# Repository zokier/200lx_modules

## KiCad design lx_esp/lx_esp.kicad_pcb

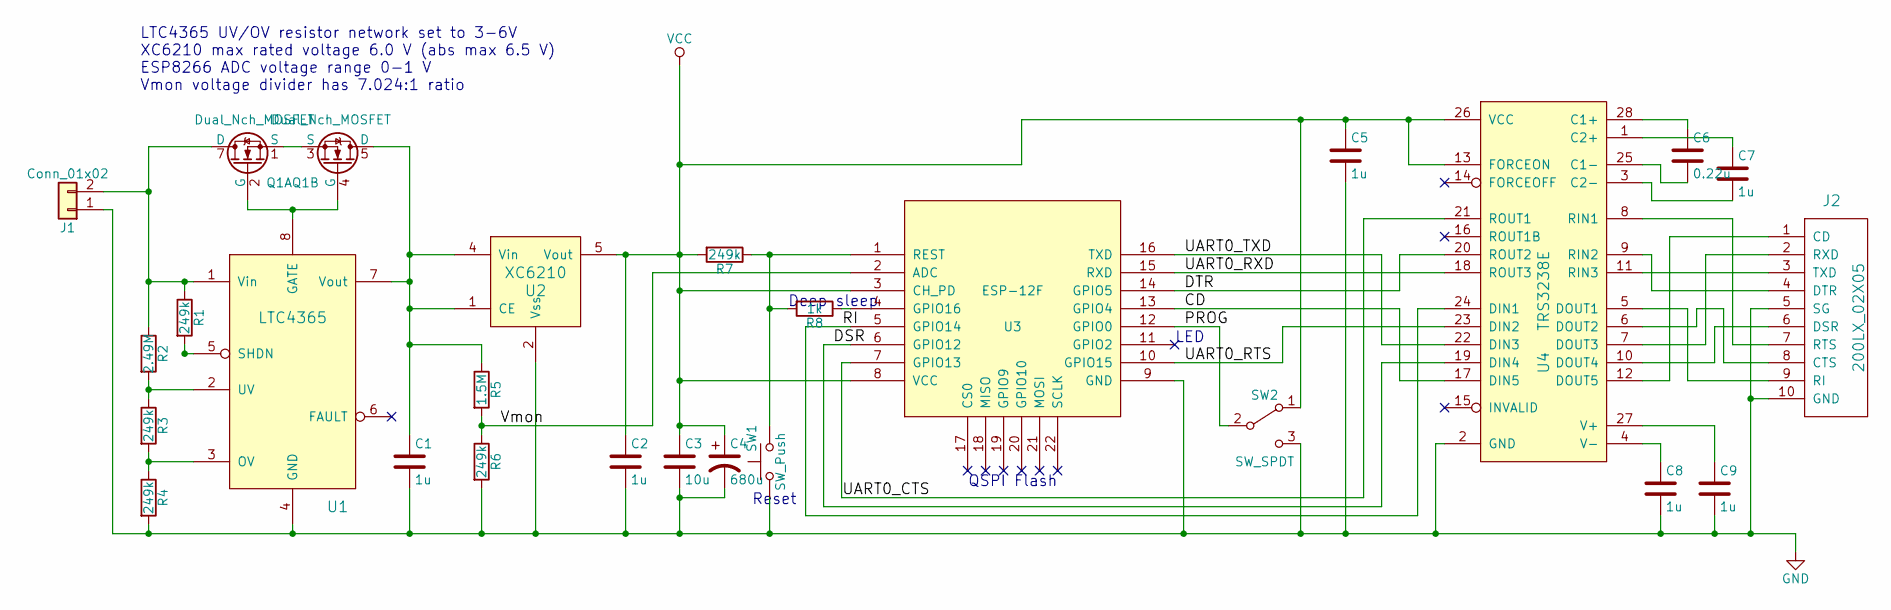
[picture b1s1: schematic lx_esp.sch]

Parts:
C1, C2, C5, C7, C8, C9: 1u; C_0805_HandSoldering
C3: 10u; C_0805_HandSoldering
C4: 680u; CP_Radial_D10.0mm_P5.00mm
C6: 0.22u; C_0805_HandSoldering
J1: Conn_01x02; JST_PH_S2B-PH-K_02x2.00mm_Angled
J2: 200LX_02X05; CONN_02x05_2mm
Q1: Dual_Nch_MOSFET; SOIC-8_3.9x4.9mm_Pitch1.27mm
R1, R3, R4, R6, R7: 249k; R_0805_HandSoldering
R2: 2.49M; R_0805_HandSoldering
R5: 1.5M; R_0805_HandSoldering
R8: 1k; R_0805_HandSoldering
SW1: SW_Push; TL3305
SW2: SW_SPDT; CL-SB-12B-02T
U1: LTC4365; TSOT-23-8_HandSoldering
U2: XC6210; SOT-89-5_Housing_Handsoldering
U3: ESP-12F; ESP-12E_SMD
U4: TRS3238E; (T)SSOP-28

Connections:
/CD: U3.13 (GPIO4), U4.17 (DIN5)
/DSR: U3.6 (GPIO12), U4.19 (DIN4)
/DTR: U3.14 (GPIO5), U4.20 (ROUT2)
/PROG: SW2.2 (B), U3.12 (GPIO0)
/RI: U3.5 (GPIO14), U4.24 (DIN1)
/UART0_CTS: U3.7 (GPIO13), U4.21 (ROUT1)
/UART0_RTS: U3.10 (GPIO15), U4.23 (DIN2)
/UART0_RXD: U3.15 (RXD), U4.18 (ROUT3)
/UART0_TXD: U3.16 (TXD), U4.22 (DIN3)
/Vmon: R5.2, R6.1, U3.2 (ADC)
GND: C1.2, C2.2, C3.2, C4.2, C5.2, C8.2, C9.2, J1.1, J2.5 (SG), J2.10 (GND), R4.2, R6.2, SW1.1, SW2.3 (C), U1.4 (GND), U2.2 (Vss), U3.9 (GND), U4.2 (GND)
unnamed: C1.1, Q1.5 (D), Q1.6 (D), R5.1, U1.7 (Vout), U2.1 (CE), U2.4 (Vin)
unnamed: C6.1, U4.28 (C1+)
unnamed: C6.2, U4.25 (C1-)
unnamed: C7.1, U4.1 (C2+)
unnamed: C7.2, U4.3 (C2-)
unnamed: C8.1, U4.4 (V-)
unnamed: C9.1, U4.27 (V+)
unnamed: J1.2, Q1.7 (D), Q1.8 (D), R1.1, R2.1, U1.1 (Vin)
unnamed: J2.1 (CD), U4.12 (DOUT5)
unnamed: J2.2 (RXD), U4.7 (DOUT3)
unnamed: J2.3 (TXD), U4.11 (RIN3)
unnamed: J2.4 (DTR), U4.9 (RIN2)
unnamed: J2.6 (DSR), U4.10 (DOUT4)
unnamed: J2.7 (RTS), U4.8 (RIN1)
unnamed: J2.8 (CTS), U4.6 (DOUT2)
unnamed: J2.9 (RI), U4.5 (DOUT1)
unnamed: Q1.1 (S), Q1.3 (S)
unnamed: Q1.2 (G), Q1.4 (G), U1.8 (GATE)
unnamed: R1.2, U1.5 (SHDN)
unnamed: R2.2, R3.1, U1.2 (UV)
unnamed: R3.2, R4.1, U1.3 (OV)
unnamed: R7.1, R8.2, SW1.2, U3.1 (REST)
unnamed: R8.1, U3.4 (GPIO16)
VCC: C2.1, C3.1, C4.1, C5.1, R7.2, SW2.1 (A), U2.5 (Vout), U3.3 (CH_PD), U3.8 (VCC), U4.13 (FORCEON), U4.26 (VCC)

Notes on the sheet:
LED
QSPI Flash
Deep sleep
Reset
LTC4365 UV/OV resistor network set to 3-6V XC6210 max rated voltage 6.0 V (abs max 6.5 V) ESP8266 ADC voltage range 0-1 V Vmon voltage divider has 7.024:1 ratio

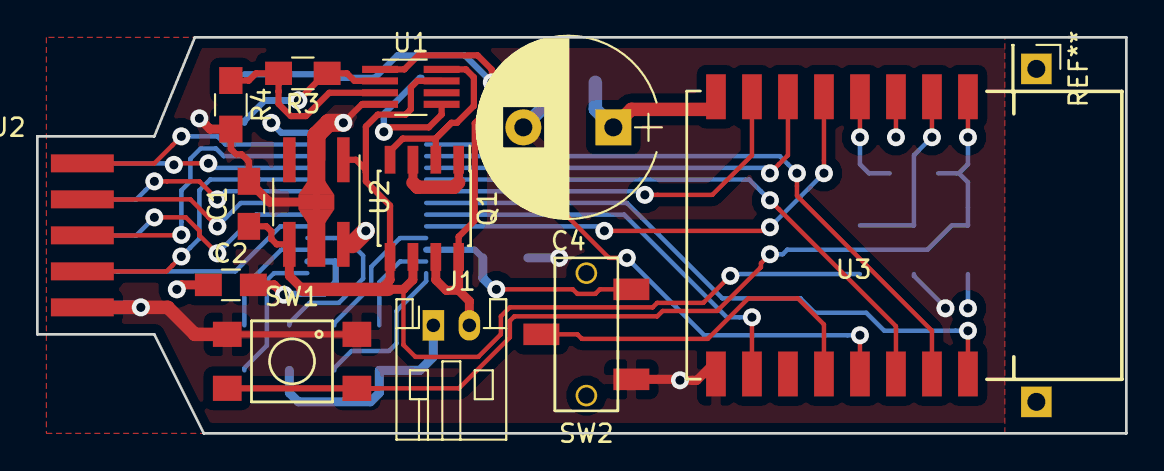
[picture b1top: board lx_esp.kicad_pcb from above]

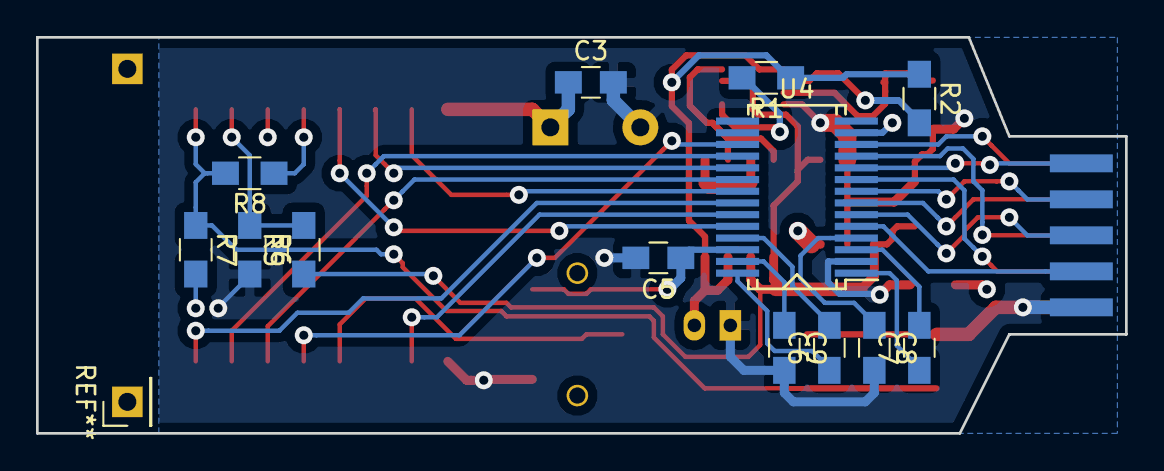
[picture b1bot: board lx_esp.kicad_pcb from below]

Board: 4 copper layers, 60.5 x 22.0 mm, 26 parts (13 on the bottom side), 35 nets.

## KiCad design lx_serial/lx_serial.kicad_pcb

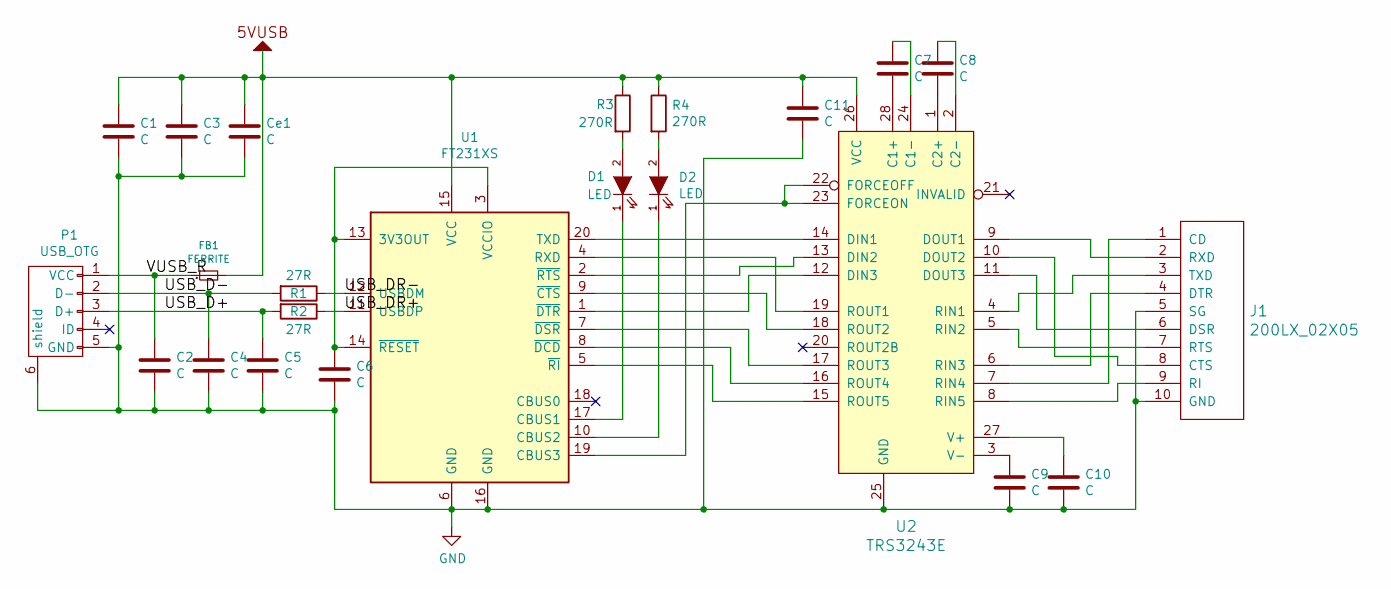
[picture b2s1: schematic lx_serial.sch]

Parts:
C1, C2, C3, C4, C5, C6, C7, C8, C9, C10, C11: C; C_0805_HandSoldering
Ce1: C; C_0805_HandSoldering
D1, D2: LED; LED_0805_HandSoldering
FB1: FERRITE; R_0805_HandSoldering
J1: 200LX_02X05; CONN_02x05_2mm
P1: USB_OTG; MICRO_USB_B_TYPE_RECEPTABLE_CIRCLES
R1, R2: 27R; R_0805_HandSoldering
R3, R4: 270R; R_0805_HandSoldering
U1: FT231XS; SSOP-20_3.9mm
U2: TRS3243E; TSSOP-28

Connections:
5VUSB: C1.1, C3.1, C11.1, Ce1.1, FB1.2, R3.1, R4.1, U1.15 (VCC), U2.26 (VCC)
/USB_D+: C5.1, P1.3 (D+), R2.2
/USB_D-: C4.1, P1.2 (D-), R1.2
/USB_DR+: R2.1, U1.11 (USBDP)
/USB_DR-: R1.1, U1.12 (USBDM)
/VUSB_R: C2.1, FB1.1, P1.1 (VCC)
unnamed: C6.2, U1.3 (VCCIO), U1.13 (3V3OUT), U1.14 (~RESET)
unnamed: C7.1, U2.24 (C1-)
unnamed: C7.2, U2.28 (C1+)
unnamed: C8.1, U2.2 (C2-)
unnamed: C8.2, U2.1 (C2+)
unnamed: C9.1, U2.3 (V-)
unnamed: C10.1, U2.27 (V+)
unnamed: D1.1 (K), U1.17 (CBUS1)
unnamed: D1.2 (A), R3.2
unnamed: D2.1 (K), U1.10 (CBUS2)
unnamed: D2.2 (A), R4.2
unnamed: J1.1 (CD), U2.7 (RIN4)
unnamed: J1.2 (RXD), U2.9 (DOUT1)
unnamed: J1.3 (TXD), U2.4 (RIN1)
unnamed: J1.4 (DTR), U2.6 (RIN3)
unnamed: J1.6 (DSR), U2.11 (DOUT3)
unnamed: J1.7 (RTS), U2.5 (RIN2)
unnamed: J1.8 (CTS), U2.10 (DOUT2)
unnamed: J1.9 (RI), U2.8 (RIN5)
unnamed: U1.1 (~DTR), U2.12 (DIN3)
unnamed: U1.2 (~RTS), U2.13 (DIN2)
unnamed: U1.4 (RXD), U2.19 (ROUT1)
unnamed: U1.5 (~RI), U2.15 (ROUT5)
unnamed: U1.7 (~DSR), U2.17 (ROUT3)
unnamed: U1.8 (~DCD), U2.16 (ROUT4)
unnamed: U1.9 (~CTS), U2.18 (ROUT2)
unnamed: U1.19 (CBUS3), U2.22 (FORCEOFF), U2.23 (FORCEON)
unnamed: U1.20 (TXD), U2.14 (DIN1)

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
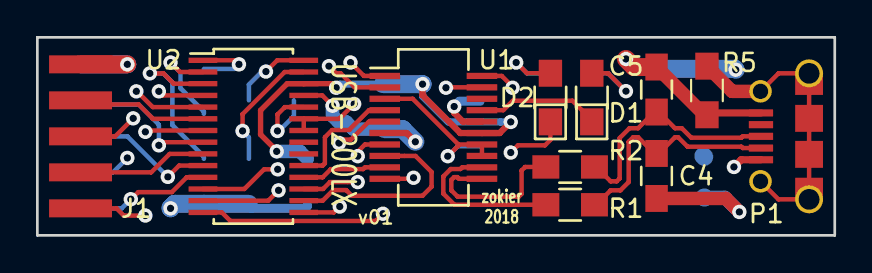
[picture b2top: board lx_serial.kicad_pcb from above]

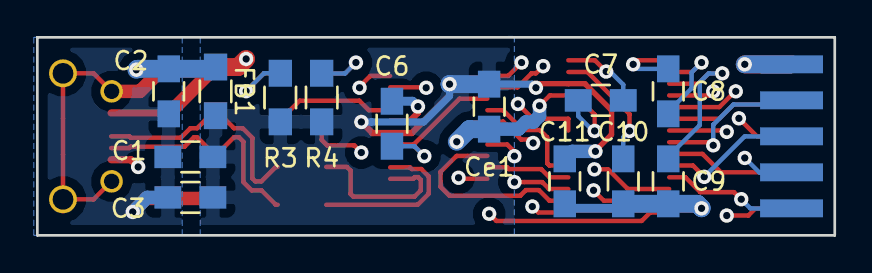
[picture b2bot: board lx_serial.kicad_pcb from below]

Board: 4 copper layers, 44.3 x 11.0 mm, 24 parts (13 on the bottom side), 36 nets.

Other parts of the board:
R5: 0R; R_0805_HandSoldering

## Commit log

2018-02-13 gitignore
2018-02-18 disconnected usb shield from gnd
2018-02-18 silkscreen tweaks
2018-02-21 add esp library submodule
2018-02-21 beginnings of esp module
2018-02-24 programming header for esp module
2018-02-24 disconnect shield from gnd in usb serial module
2018-02-25 LTC4365
2018-02-26 new power supply
2018-03-03 Swap TRS3243 to TRS3238
2018-03-03 add XC6210 datasheet
2018-03-04 footprint for ssop28 (compatible with tssop)
2018-03-04 ltc4365 datasheet
2018-03-04 assign footprints for chips
2018-03-05 footprints and designators and stuff
2018-03-06 footprints for passives
2018-03-09 footprints for switches
2018-03-09 move datasheets to own directory
2018-03-10 PCB layout
2018-03-10 DMG9926 datasheet
2018-03-10 more pcb layout
2018-03-10 pcb tweaks
2018-03-11 narrower pcb for esp
